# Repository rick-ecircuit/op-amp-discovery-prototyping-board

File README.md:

# Op Amp Discovery Board
## Fast & Veratile Prototyping and Experimenter Board
The Op Amp Discovery Board allows students, engineers and DIYers to quickly prototype and experiment with a variety of op amp configurations. Get circuits up and running fast! Serves as a Trainer Board as well as an Evaluation Module.

- Easy-to-use hybrid (solderless breadboard + PCB).
- Explore 20+ classic op amp circuits
- Create your own circuits
- Supply Rails & Signal Source Included on-board

Hands-on trainer boosts understanding and intuition!
- Flexible - easily install Rs, Cs or jumpers across any headers.
- Fun problem solving - How-to-build circuit on available component headers?
- Configurable signal - DC, AC, square-wave, level trimpot
- Powered by 9V Battery

Standard breadboards can be frustrating:
- Prone to opens, shorts, intermittent connections
- Confusing, difficult to probe and debug
- Requires expensive, bulky supplies and signal generators

Op Amp Discovery:
- PCB provides solid, versatile connections, power and a signal source.
- Components easily installed on solderless headers.
- Layout arranged like schematic to reinforce learning.
- Minimal cost and PCB space - an affordable & portable learn-anywhere lab.
- Learning possible with a $10 DMM only.

## Users Guide (PDF)
- Quick Start Guide 
- Description, Schematics, BOM
- Proto-Area Schematic, Bonus Sections

## Example Circuits - Guided Learning (PDF)
- Guided examples of classic op amp circuits
- Define It, Design It, Build It, Test & Learn It

## Feedback, Comments, Questions?
Share your thoughts on the [eCircuit Center](https://ecircuitcenter.com/op-amp-discovery/form/feedback1.html) feedback form.

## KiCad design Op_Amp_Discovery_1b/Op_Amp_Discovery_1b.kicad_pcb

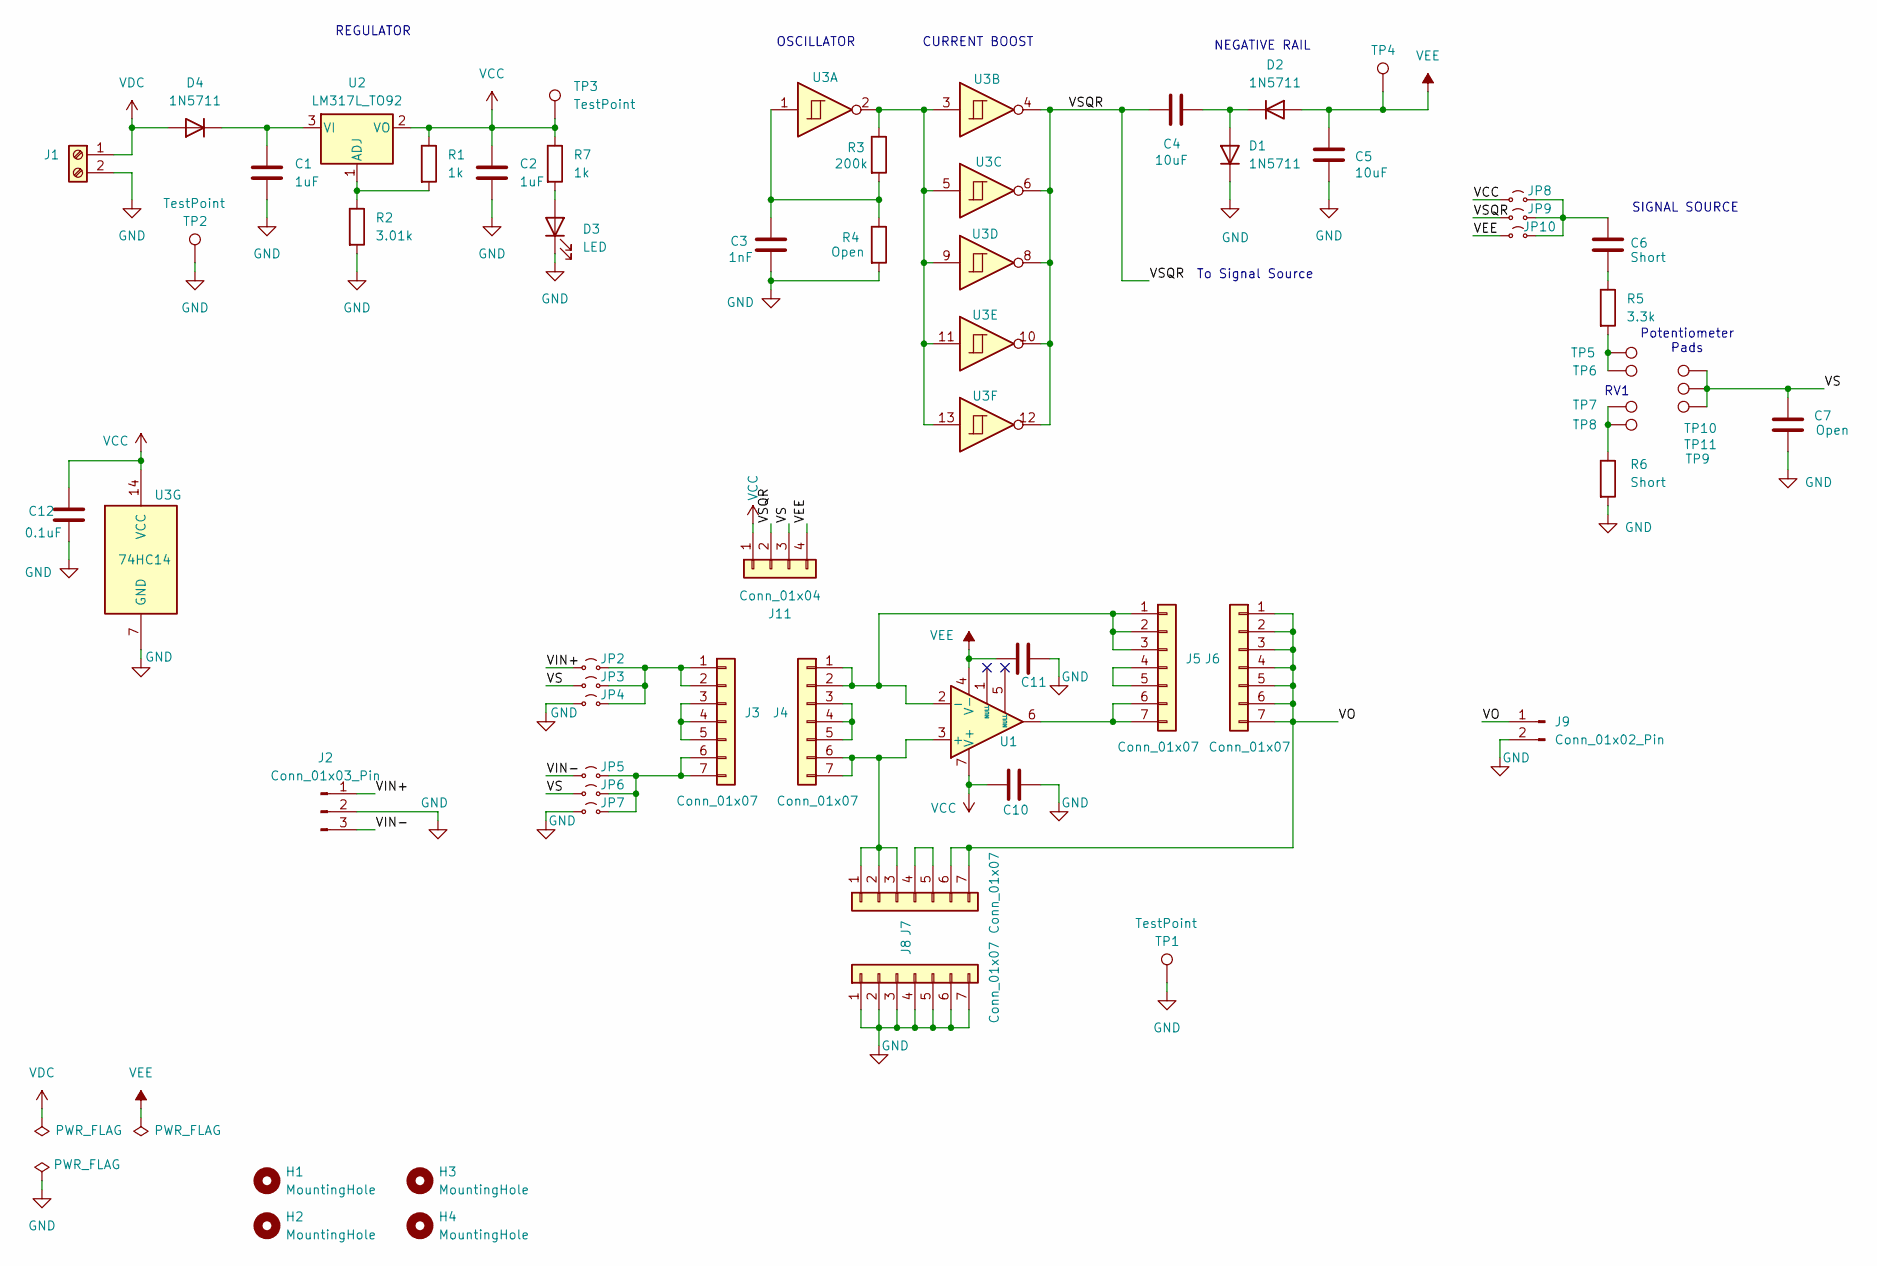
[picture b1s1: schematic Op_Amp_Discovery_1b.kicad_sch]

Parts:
C1, C2: 1uF; C_Disc_D3.0mm_W1.6mm_P2.50mm_wider_center_dia
C3: 1nF; C_Disc_D3.0mm_W1.6mm_P2.50mm_wider_center_dia
C4, C5: 10uF; C_Disc_D3.0mm_W1.6mm_P2.50mm_wider_center_dia
C6: Short; C_Disc_D3.0mm_W1.6mm_P2.50mm_wider_center_dia
C7: Open; C_Disc_D3.0mm_W1.6mm_P2.50mm_wider_center_dia
C10, C11, C12: 0.1uF; C_Disc_D3.0mm_W1.6mm_P2.50mm_wider_center_dia
D1, D2, D4: 1N5711; D_DO-34_SOD68_P7.62mm_Horizontal
D3: LED; LED_D3.0mm
H1, H2, H3, H4: MountingHole; MountingHole_3.7mm
J1: Screw_Terminal_01x02; TerminalBlock_bornier-2_P5.08mm
J2: Conn_01x03_Pin; PinHeader_1x03_P2.54mm_Vertical
J3, J4, J5, J6, J7, J8: Conn_01x07; PinSocket_1x07_P2.54mm_Vertical
J9: Conn_01x02_Pin; PinHeader_1x02_P2.54mm_Vertical
J11: Conn_01x04; PinSocket_1x04_P2.54mm_Vertical
JP2, JP3, JP4, JP5, JP6, JP7, JP8, JP9, JP10: Jumper_2_Small_Open; PinHeader_1x02_P2.54mm_Vertical
R1, R7: 1k; R_Axial_DIN0204_L3.6mm_D1.6mm_P7.62mm_Horizontal-bigger_hole
R2: 3.01k; R_Axial_DIN0204_L3.6mm_D1.6mm_P7.62mm_Horizontal-bigger_hole
R3: 200k; R_Axial_DIN0204_L3.6mm_D1.6mm_P7.62mm_Horizontal-bigger_hole
R4: Open; R_Axial_DIN0204_L3.6mm_D1.6mm_P7.62mm_Horizontal-bigger_hole
R5: 3.3k; R_Axial_DIN0204_L3.6mm_D1.6mm_P7.62mm_Horizontal-bigger_hole
R6: Short; R_Axial_DIN0204_L3.6mm_D1.6mm_P7.62mm_Horizontal-bigger_hole
TP1: TestPoint; TestPoint_Keystone_5005-5009_Compact
TP2, TP3, TP4, TP5, TP6, TP7, TP8, TP9, TP10, TP11: TestPoint; TestPoint_THTPad_D2.0mm_Drill1.0mm_bigger
U1: LM741; DIP-8_W7.62mm
U2: LM317L_TO92; TO-92_Inline_Wide
U3: 74HC14; DIP-14_W7.62mm

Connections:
/VIN+: J2.1, JP2.1 (A)
/VIN-: J2.3, JP5.1 (A)
/VO: J6.1, J6.2, J6.3, J6.4, J6.5, J6.6, J6.7, J7.6, J7.7, J9.1
/VS: C7.1, J11.3, JP3.1 (A), JP6.1 (A), TP9.1, TP10.1, TP11.1
/VSQR: C4.1, J11.2, JP9.1 (A), U3.4, U3.6, U3.8, U3.10, U3.12
GND: C1.2, C2.2, C3.2, C5.2, C7.2, C10.2, C11.2, C12.2, D1.1 (K), D3.1 (K), J1.2, J2.2, J8.1, J8.2, J8.3, J8.4, J8.5, J8.6, J8.7, J9.2, JP4.1 (A), JP7.1 (A), R2.2, R4.2, R6.2, TP1.1, TP2.1, U3.7 (GND)
unnamed: C3.1, R3.2, R4.1, U3.1
unnamed: C6.2, R5.1
unnamed: C4.2, D1.2 (A), D2.1 (K)
unnamed: D3.2 (A), R7.2
unnamed: C1.1, D4.1 (K), U2.3 (VI)
unnamed: J3.1, J3.2, JP2.2 (B), JP3.2 (B), JP4.2 (B)
unnamed: J3.3, J3.4, J3.5
unnamed: J3.6, J3.7, JP5.2 (B), JP6.2 (B), JP7.2 (B)
unnamed: J4.1, J4.2, J5.1, J5.2, J5.3, U1.2 (-)
unnamed: J4.3, J4.4, J4.5
unnamed: J4.6, J4.7, J7.1, J7.2, J7.3, U1.3 (+)
unnamed: J5.4, J5.5
unnamed: J5.6, J5.7, U1.6
unnamed: J7.4, J7.5
unnamed: C6.1, JP8.2 (B), JP9.2 (B), JP10.2 (B)
unnamed: R3.1, U3.2, U3.3, U3.5, U3.9, U3.11, U3.13
unnamed: R5.2, TP5.1, TP6.1
unnamed: R6.1, TP7.1, TP8.1
unnamed: R1.2, R2.1, U2.1 (ADJ)
VCC: C2.1, C10.1, C12.1, J11.1, JP8.1 (A), R1.1, R7.1, TP3.1, U1.7 (V+), U2.2 (VO), U3.14 (VCC)
VDC: D4.2 (A), J1.1
VEE: C5.1, C11.1, D2.2 (A), J11.4, JP10.1 (A), TP4.1, U1.4 (V-)

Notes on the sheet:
OSCILLATOR
To Signal Source
CURRENT BOOST
NEGATIVE RAIL
Potentiometer Pads
REGULATOR
SIGNAL SOURCE
RV1

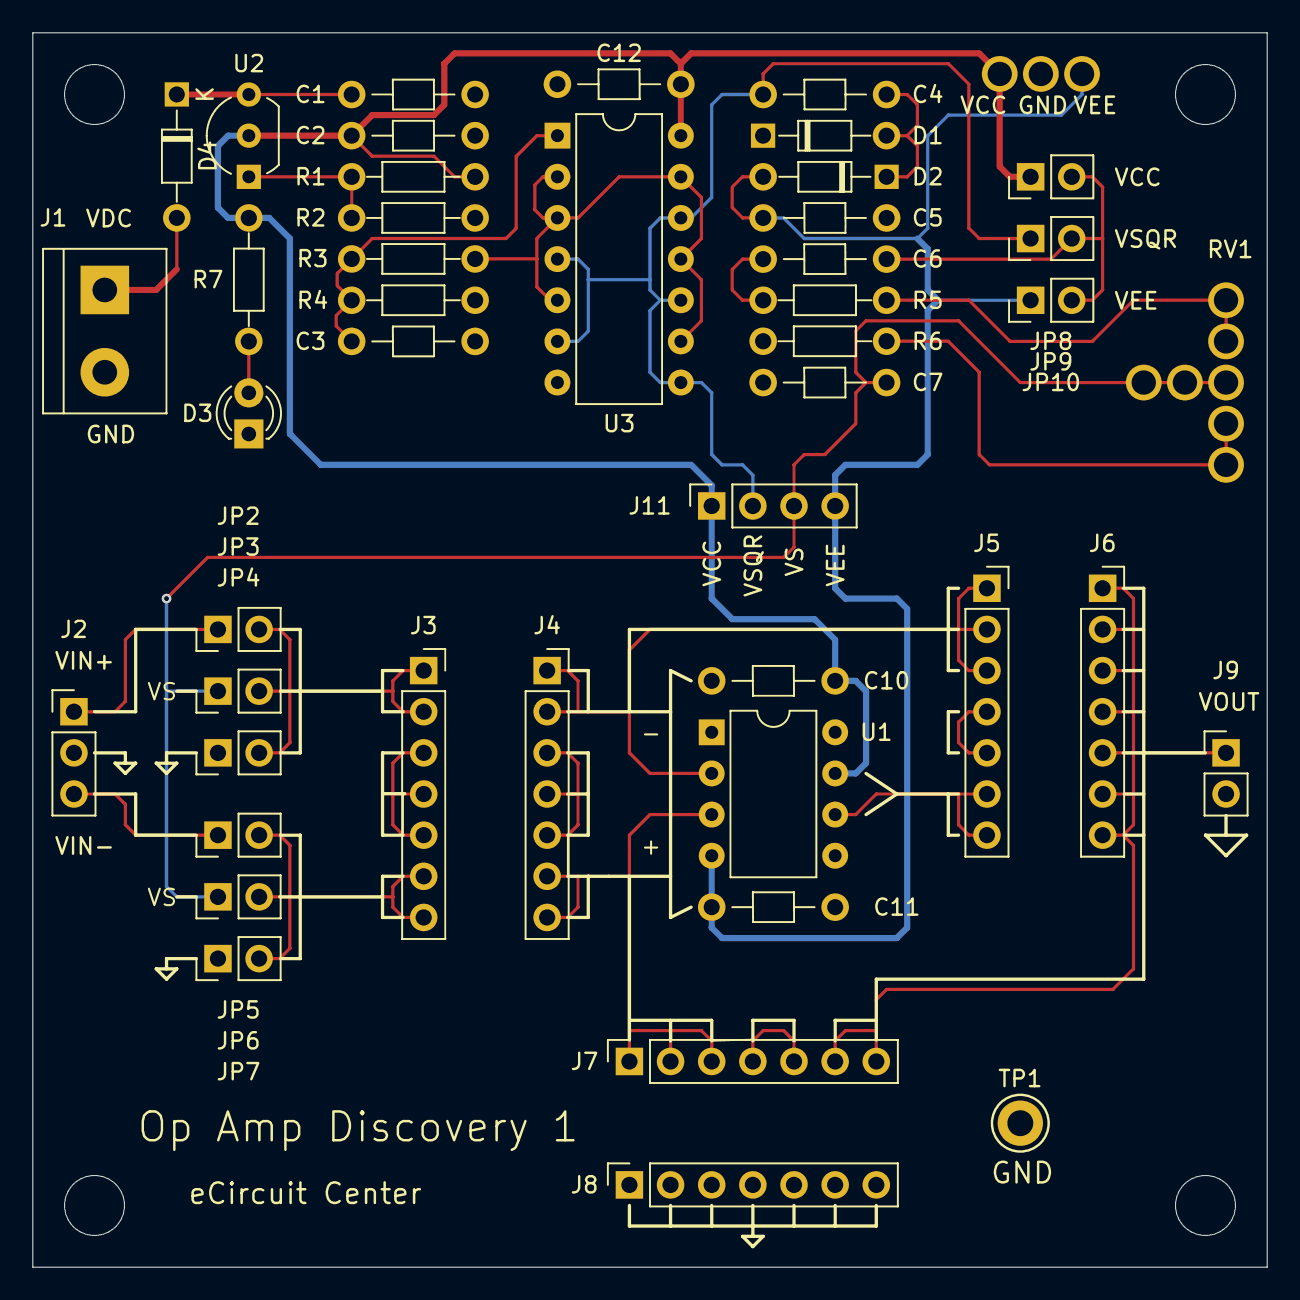
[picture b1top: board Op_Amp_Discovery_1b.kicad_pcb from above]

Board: 2 copper layers, 76.2 x 76.2 mm, 58 parts (0 on the bottom side), 28 nets.

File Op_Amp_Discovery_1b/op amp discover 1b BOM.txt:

Reference	Value	Datasheet	Footprint	Qty	DNP
C1,C2	1uF	~	A_Custom_Library:C_Disc_D3.0mm_W1.6mm_P2.50mm_wider_center_dia	2	
C3	1nF	~	A_Custom_Library:C_Disc_D3.0mm_W1.6mm_P2.50mm_wider_center_dia	1	
C4,C5	10uF	~	A_Custom_Library:C_Disc_D3.0mm_W1.6mm_P2.50mm_wider_center_dia	2	
C6,R6	Short	~	A_Custom_Library:C_Disc_D3.0mm_W1.6mm_P2.50mm_wider_center_dia,A_Custom_Library:R_Axial_DIN0204_L3.6mm_D1.6mm_P7.62mm_Horizontal-bigger_hole	2	
C7,R4	Open	~	A_Custom_Library:C_Disc_D3.0mm_W1.6mm_P2.50mm_wider_center_dia,A_Custom_Library:R_Axial_DIN0204_L3.6mm_D1.6mm_P7.62mm_Horizontal-bigger_hole	2	
C10,C11,C12	0.1uF	~	A_Custom_Library:C_Disc_D3.0mm_W1.6mm_P2.50mm_wider_center_dia	3	
D1,D2,D4	1N5711	~	A_Custom_Library:D_DO-34_SOD68_P7.62mm_Horizontal	3	
D3	LED	~	LED_THT:LED_D3.0mm	1	
J1	Screw_Terminal_01x02	~	TerminalBlock:TerminalBlock_bornier-2_P5.08mm	1	
J2	Conn_01x03_Pin	~	Connector_PinHeader_2.54mm:PinHeader_1x03_P2.54mm_Vertical	1	
J3,J4,J5,J6,J7,J8	Conn_01x07	~	Connector_PinSocket_2.54mm:PinSocket_1x07_P2.54mm_Vertical	6	
J9	Conn_01x02_Pin	~	Connector_PinHeader_2.54mm:PinHeader_1x02_P2.54mm_Vertical	1	
J11	Conn_01x04	~	Connector_PinSocket_2.54mm:PinSocket_1x04_P2.54mm_Vertical	1	
JP2,JP3,JP4,JP5,JP6,JP7,JP8,JP9,JP10	Jumper_2_Small_Open	~	Connector_PinHeader_2.54mm:PinHeader_1x02_P2.54mm_Vertical	9	
R1,R7	1k	~	A_Custom_Library:R_Axial_DIN0204_L3.6mm_D1.6mm_P7.62mm_Horizontal-bigger_hole	2	
R2	3.01k	~	A_Custom_Library:R_Axial_DIN0204_L3.6mm_D1.6mm_P7.62mm_Horizontal-bigger_hole	1	
R3	200k	~	A_Custom_Library:R_Axial_DIN0204_L3.6mm_D1.6mm_P7.62mm_Horizontal-bigger_hole	1	
R5	3.3k	~	A_Custom_Library:R_Axial_DIN0204_L3.6mm_D1.6mm_P7.62mm_Horizontal-bigger_hole	1	
TP1,TP2,TP3,TP4,TP5,TP6,TP7,TP8,TP9,TP10,TP11	TestPoint	~	A_Custom_Library:TestPoint_THTPad_D2.0mm_Drill1.0mm_bigger,TestPoint:TestPoint_Keystone_5005-5009_Compact	11	
U1	LM741	http://www.ti.com/lit/ds/symlink/lm741.pdf	Package_DIP:DIP-8_W7.62mm	1	
U2	LM317L_TO92	http://www.ti.com/lit/ds/snvs775k/snvs775k.pdf	Package_TO_SOT_THT:TO-92_Inline_Wide	1	
U3	74HC14	http://www.ti.com/lit/gpn/sn74HC14	Package_DIP:DIP-14_W7.62mm	1

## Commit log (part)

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2026-01-05 Initial readme and uploads
    Initial readme edit, PDF, KiCAD upload
2026-01-05 Add pcb image
2026-01-08 update users guide, pcb image
2026-01-11 update zip folder, add sch (pdf)
2026-01-15 update users guide, readme
    also remove kiCAD backups
2026-01-20 Add Excel calc, update users guide
2026-01-23 Update users, example, excel, readme
2026-01-23 rename pdfs, edit excel
2026-02-23 Update README.md
    add trainer, evaluation module
